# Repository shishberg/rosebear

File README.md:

# Rosebear

## Current chassis-based design

The current design is v4: bought RGB key tiles hand-wired in a 3D-printed chassis, with an ESP32-P4 pod. Start with the [v4 README](v4/README.md) and [design status](v4/docs/design-status.md).

The active chassis tool is the [TypeScript browser editor](v4/editor/README.md): run `make v4-editor` and open http://127.0.0.1:5177. Drag handles on the key layout, with live surfaces and automatic cutout/clearance rebuilds in Manifold WASM. KiCad generation remains offline. The previous [Python foundation](v4/docs/chassis-foundation.md) and its exported previews are retained as references. The description below covers the original flat Choc keyboard.

Rosebear is a 5x3+3 wireless split keyboard designed with [Ergogen](https://ergogen.xyz/). ZMK firmware is at https://github.com/shishberg/rosebear-zmk.

Thanks to [Ben Vallack](https://www.youtube.com/watch?v=M_VuXVErD6E) and [FlatFootFox](https://flatfootfox.com/ergogen-part5-kicad-firmware-assembly/) for the tutorials that made this even vaguely possible.

## Features
- Pretty aggressive stagger on the pinky column, and splay on pinky and ring columns
- Thumb cluster is waaaaay over there
- Direct pin wiring - no diodes
- Kailh choc switches - supports hotswap or soldered
- Bluetooth only (there aren't any pins available for a cable between the two sides)

## Lessons learnt
- Don't use a JST connector for the battery. Just don't. You don't need to. Crimping is fiddly as hell (I don't have a crimper and don't really want to buy one). Even if the battery comes with one, it's annoying as hell to unplug. Just solder the battery terminals on. If you want to replace or reuse the battery, unsoldering two wires is trivial.
  - I used a JST connector on the left board, but it was too hard so for the right board I just soldered the battery on. That was so much easier that it made me so mad that I unsoldered the connector from the left board, which was harder again; and then I soldered the battery in the wrong way around, which nearly burned out the nice!nano.
  - The picture above doesn't have a reset button because they haven't arrived yet.
- There _might_ be such a thing as too much pinky stagger. Or I might just need longer to get used to it.
- If you're not going to use a bottom plate, it would help to plan some empty spaces to put rubber feet.
  - PCBs don't come perfectly flat. If you're going to use rubber feet, you either need to use exactly three (and the triangle they form needs to cover all the keys or it'll rock when you press a key outside it); or you need to adjust their height (which I ended up doing with some ~1mm thick two-sided adhesive dots that I happened to have)
- I do like having the thumb cluster further out. I intended for the middle thumb key to be the "home" key (space and enter for me) and the one you have to stretch for can be something less common (esc and del). That's fine, but I should have made middle key 1.5u so it's easy to find.
- Choc pinks are so light they almost type by themselves under the weight of keycaps. I'd used dark yellows before and found them too heavy. Reds are about right.
- Choc keycaps could do with a bit of spacing between them vertically. Especially with very light switches, it's too easy to accidentally brush another key.

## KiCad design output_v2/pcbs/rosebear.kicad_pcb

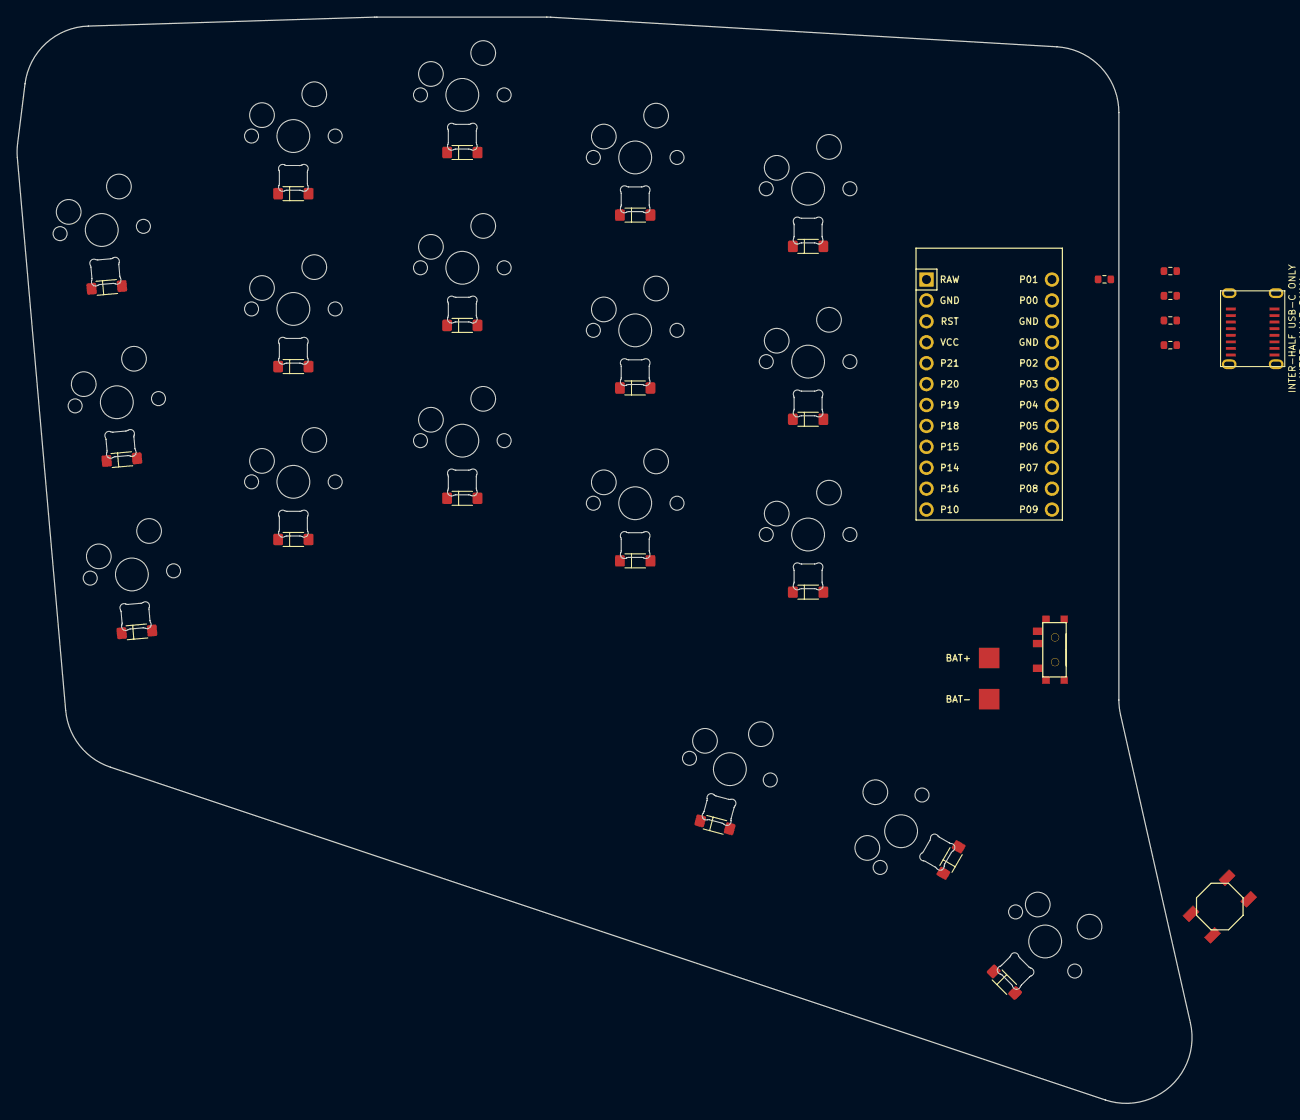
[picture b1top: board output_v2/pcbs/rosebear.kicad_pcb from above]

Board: 2 copper layers, 142.7 x 131.9 mm, 65 parts (0 on the bottom side), 60 nets, no tracks yet.

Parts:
B1: SW_TACT_ALPS_SKQGABE010
D1, D2, D3, D4, D5, D6, D7, D8, D9, D10, D11, D12, D13, D14, D15, D16, D17, D18: SOD-123
J1: INTER-HALF USB-C ONLY; USB-C_inter_half_placeholder
LED1, LED2, LED3, LED4, LED5, LED6, LED7, LED8, LED9, LED10, LED11, LED12, LED13, LED14, LED15, LED16, LED17, LED18: SK6812MINI-E; SK6812MINI-E_MX-reverse
MCU1: ProMicro
PAD1, PAD2: SMDPad
R1, R2, R3, R4, R5: R_0603; R_0603_1608Metric
S1, S2, S3, S4, S5, S6, S7, S8, S9, S10, S11, S12, S13, S14, S15, S16, S17, S18: MX
T1: SPDT_C128955

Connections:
Bplus: PAD1.1, T1.1
COL0: MCU1.8, S1.1, S2.1, S3.1
COL1: MCU1.9, S4.1, S5.1, S6.1
COL2: MCU1.10, S7.1, S8.1, S9.1
COL3: MCU1.11, S10.1, S11.1, S12.1
COL4: MCU1.12, S13.1, S14.1, S15.1
COL5: MCU1.13, S16.1, S17.1, S18.1
GND: B1.1, J1.A1, J1.A12, J1.B1, J1.B12, J1.S1, J1.S2, J1.S3, J1.S4, LED1.3, LED2.3, LED3.3, LED4.3, LED5.3, LED6.3, LED7.3, LED8.3, LED9.3, LED10.3, LED11.3, LED12.3, LED13.3, LED14.3, LED15.3, LED16.3, LED17.3, LED18.3, MCU1.2, MCU1.15, MCU1.16, PAD2.1
IH_DETECT_CONN: J1.A5, J1.B5, R4.2
IH_DETECT_MCU: MCU1.19, R4.1
IH_RX_CONN: J1.A7, J1.B7, R3.2
IH_RX_MCU: MCU1.18, R3.1
IH_SPARE_CONN: J1.A8, J1.B8, R5.2
IH_SPARE_MCU: MCU1.20, R5.1
IH_TX_CONN: J1.A6, J1.B6, R2.2
IH_TX_MCU: MCU1.17, R2.1
LED_01: LED3.2, LED6.4
LED_02: LED6.2, LED9.4
LED_03: LED9.2, LED12.4
LED_04: LED12.2, LED15.4
LED_05: LED14.4, LED15.2
LED_06: LED11.4, LED14.2
LED_07: LED8.4, LED11.2
LED_08: LED5.4, LED8.2
LED_09: LED2.4, LED5.2
LED_10: LED1.4, LED2.2
LED_11: LED1.2, LED4.4
LED_12: LED4.2, LED7.4
LED_13: LED7.2, LED10.4
LED_14: LED10.2, LED13.4
LED_15: LED13.2, LED16.4
LED_16: LED16.2, LED17.4
LED_17: LED17.2, LED18.4
LED_DATA_MCU: MCU1.14, R1.1
LED_DIN: LED3.4, R1.2
LED_VDD: LED1.1, LED2.1, LED3.1, LED4.1, LED5.1, LED6.1, LED7.1, LED8.1, LED9.1, LED10.1, LED11.1, LED12.1, LED13.1, LED14.1, LED15.1, LED16.1, LED17.1, LED18.1
RAW: MCU1.1, T1.2
ROW0: D3.1, D6.1, D9.1, D12.1, D15.1, D18.1, MCU1.5
ROW1: D2.1, D5.1, D8.1, D11.1, D14.1, D17.1, MCU1.6
ROW2: D1.1, D4.1, D7.1, D10.1, D13.1, D16.1, MCU1.7
RST: B1.2, MCU1.3
WIRED_5V: J1.A4, J1.A9, J1.B4, J1.B9
matrix_index_bottom_SW: D10.2, S10.2
matrix_index_home_SW: D11.2, S11.2
matrix_index_top_SW: D12.2, S12.2
matrix_inner_bottom_SW: D13.2, S13.2
matrix_inner_home_SW: D14.2, S14.2
matrix_inner_top_SW: D15.2, S15.2
matrix_middle_bottom_SW: D7.2, S7.2
matrix_middle_home_SW: D8.2, S8.2
matrix_middle_top_SW: D9.2, S9.2
matrix_pinky_bottom_SW: D1.2, S1.2
matrix_pinky_home_SW: D2.2, S2.2
matrix_pinky_top_SW: D3.2, S3.2
matrix_ring_bottom_SW: D4.2, S4.2
matrix_ring_home_SW: D5.2, S5.2
matrix_ring_top_SW: D6.2, S6.2
thumb_far_thumb_SW: D18.2, S18.2
thumb_home_thumb_SW: D17.2, S17.2
thumb_near_thumb_SW: D16.2, S16.2

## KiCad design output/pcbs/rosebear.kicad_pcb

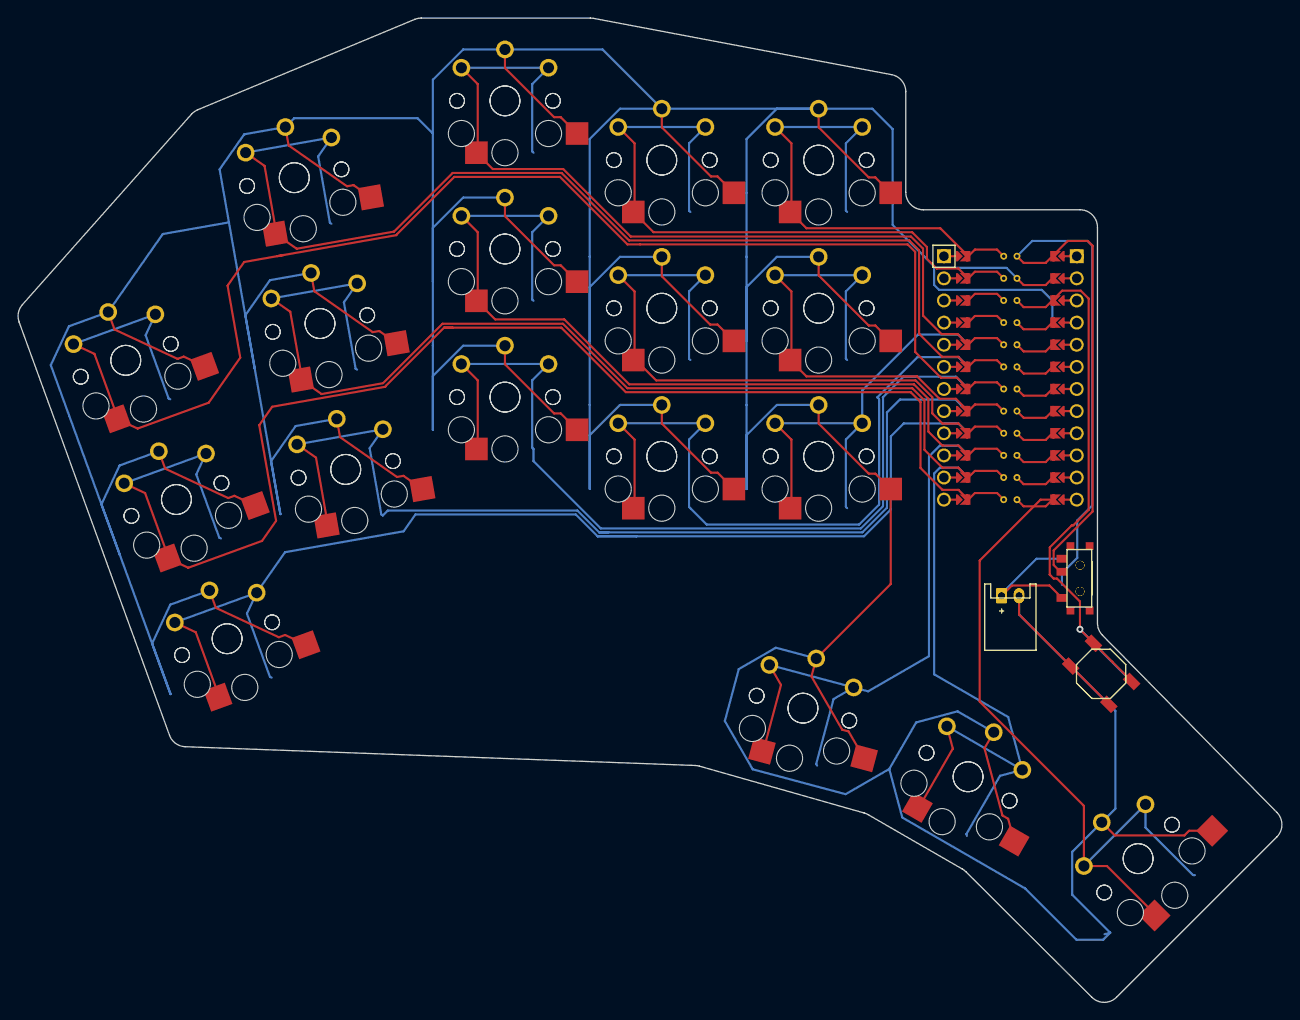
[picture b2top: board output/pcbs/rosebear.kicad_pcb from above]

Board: 2 copper layers, 145.1 x 113.0 mm, 43 parts (0 on the bottom side), 22 nets.

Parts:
B1, B2: SW_TACT_ALPS_SKQGABE010
JST1, JST2: JST_PH_S2B-PH-K_02x2.00mm_Angled
MCU1: ProMicro
S1, S2, S3, S4, S5, S6, S7, S8, S9, S10, S11, S12, S13, S14, S15, S16, S17, S18, S19, S20, S21, S22, S23, S24, S25, S26, S27, S28, S29, S30, S31, S32, S33, S34, S35, S36: PG1350
T1, T2: SPDT_C128955

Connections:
Bplus: JST1.1, JST2.1, T1.1, T2.1
GND: B1.1, B2.1, JST1.2, JST2.2, MCU1.2, MCU1.21, MCU1.22, S1.2, S2.2, S3.2, S4.2, S5.2, S6.2, S7.2, S8.2, S9.2, S10.2, S11.2, S12.2, S13.2, S14.2, S15.2, S16.2, S17.2, S18.2, S19.2, S20.2, S21.2, S22.2, S23.2, S24.2, S25.2, S26.2, S27.2, S28.2, S29.2, S30.2, S31.2, S32.2, S33.2, S34.2, S35.2, S36.2
P0: MCU1.23, S12.1, S30.1
P1: MCU1.24, S15.1, S33.1
P2: MCU1.20, S9.1, S27.1
P3: MCU1.19, S6.1, S24.1
P4: MCU1.18, S3.1, S21.1
P5: MCU1.17, S14.1, S32.1
P6: MCU1.16, S11.1, S29.1
P7: MCU1.15, S8.1, S26.1
P8: MCU1.14, S5.1, S23.1
P9: MCU1.13, S2.1, S20.1
P10: MCU1.12, S18.1, S36.1
P14: MCU1.10, S16.1, S34.1
P15: MCU1.9, S1.1, S19.1
P16: MCU1.11, S17.1, S35.1
P18: MCU1.8, S4.1, S22.1
P19: MCU1.7, S7.1, S25.1
P20: MCU1.6, S10.1, S28.1
P21: MCU1.5, S13.1, S31.1
RAW: MCU1.1, T1.2, T2.2
RST: B1.2, B2.2, MCU1.3

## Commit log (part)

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2023-07-03 initial checkin
2023-07-03 inset board edge a bit
2023-07-08 move thumb cluster out, and other adjustments
2023-07-08 move components around
2023-07-08 final-ish wiring
2023-07-31 final routing
2023-08-08 readme
2026-05-28 Add initial v2 board files
2026-05-28 Set up v2 matrix placement board
